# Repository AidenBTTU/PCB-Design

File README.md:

This repository holds the Custom PCB Design I have done during my degree so far. This includes a step counting device with I2C and USB communication, an external crystal oscillator, and a power system with battery charging capabilities aswell as a seperate PCB for driving motors.

# Step Count PCB V2

# Motor Driver PCB

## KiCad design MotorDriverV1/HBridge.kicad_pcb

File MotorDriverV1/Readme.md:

The motor driver pcb designed in this folder was designed to operate with 6V TT Motors from a Raspberry Pi Pico. A signal voltage taken off a shunt resistor is amplified on board to be sent to a seperate overcurrent detection board. The PCB is designed to be operated with 2-4 TT motors controlled in pairs. Connectors are designed with the Raspberry Pi Pico in mind. Current through motors is not designed to handle more than 2A collectively. LFWD & LREV, RFWD & RREV are exclusive pairs and should not be held high at the same time or else through-current is likely. Pull up resistors allow the board to be operated from a digital voltage supply, but signal pins have only been tested at 3.3V. Mosfets used are the readily available IRLZ44N and IRF4905. The resistor used should be 500mohm or greater if using long or thin cables, capable of handling at least 1W.

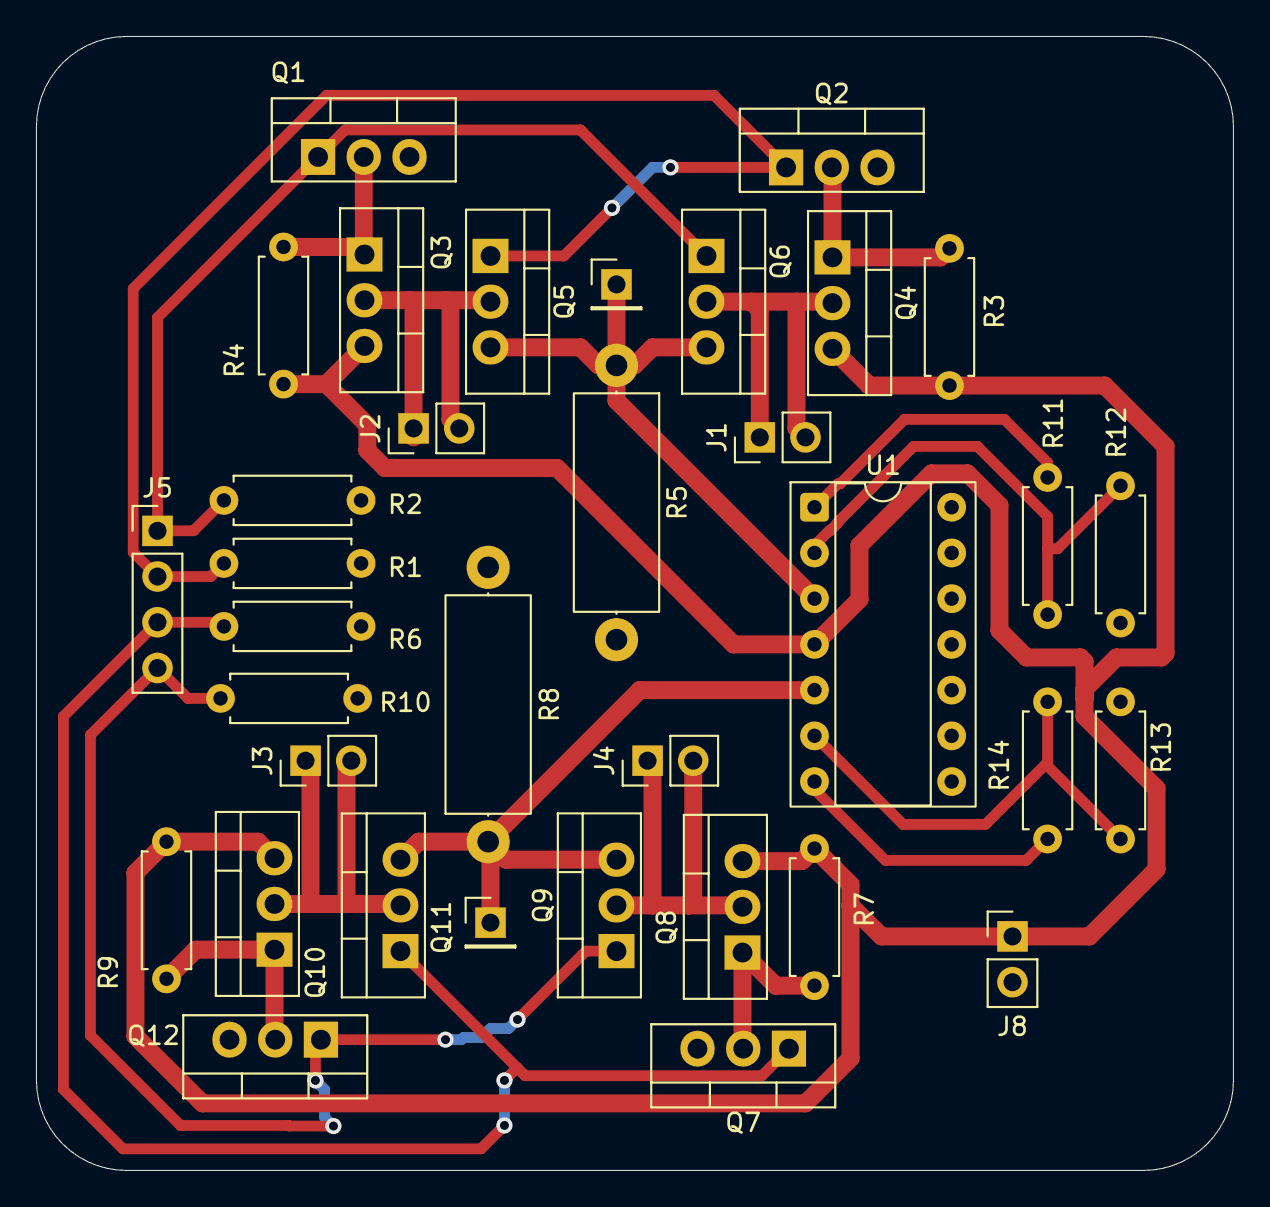
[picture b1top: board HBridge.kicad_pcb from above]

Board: 2 copper layers, 66.5 x 63.0 mm, 35 parts (0 on the bottom side), 20 nets.

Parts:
J1, J2, J3, J4, J8: Conn_01x02_Pin; PinHeader_1x02_P2.54mm_Vertical
J5: Conn_01x04_Pin; PinHeader_1x04_P2.54mm_Vertical
J6, J7: Conn_01x01_Pin; PinHeader_1x01_P2.54mm_Vertical
Q1, Q2, Q5, Q6, Q7, Q9, Q11, Q12: IRLZ44N; TO-220-3_Vertical
Q3, Q4, Q8, Q10: IRF4905; TO-220-3_Vertical
R1, R2, R3, R4, R6, R7, R9, R10: 100k; R_Axial_DIN0207_L6.3mm_D2.5mm_P7.62mm_Horizontal
R5, R8: 0.01; R_Axial_DIN0414_L11.9mm_D4.5mm_P15.24mm_Horizontal
R11, R12, R13, R14: R; R_Axial_DIN0207_L6.3mm_D2.5mm_P7.62mm_Horizontal
U1: LM324; DIP-14_W7.62mm_Socket

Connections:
+5V: J8.1, Q3.3 (S), Q4.3 (S), Q8.3 (S), Q10.3 (S), R3.2, R4.2, R7.2, R9.2, U1.4 (V+)
/LM1: J1.1, J1.2, Q4.2 (D), Q6.2 (D)
/LM2: J2.1, J2.2, Q3.2 (D), Q5.2 (D)
/Lin1: J5.2, Q2.1 (G), Q5.1 (G), R1.1
/Lin2: J5.1, Q1.1 (G), Q6.1 (G), R2.1
/Lout: R11.2, U1.1
/RM1: J3.1, J3.2, Q10.2 (D), Q11.2 (D)
/RM2: J4.1, J4.2, Q8.2 (D), Q9.2 (D)
/Rin1: J5.4, Q9.1 (G), Q12.1 (G), R10.1
/Rin2: J5.3, Q7.1 (G), Q11.1 (G), R6.1
/Rout: R14.2, U1.7
/VSL: J6.1, Q5.3 (S), Q6.3 (S), R5.1, U1.3 (+)
/VSR: J7.1, Q9.3 (S), Q11.3 (S), R8.1, U1.5 (+)
GND: J8.2, Q1.3 (S), Q2.3 (S), Q7.3 (S), Q12.3 (S), R1.2, R2.2, R5.2, R6.2, R8.2, R10.2, R12.1, R13.1, U1.11 (V-)
unnamed: Q1.2 (D), Q3.1 (G), R4.1
unnamed: Q2.2 (D), Q4.1 (G), R3.1
unnamed: Q7.2 (D), Q8.1 (G), R7.1
unnamed: Q10.1 (G), Q12.2 (D), R9.1
unnamed: R11.1, R12.2, U1.2 (-)
unnamed: R13.2, R14.1, U1.6 (-)

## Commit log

2026-04-25 Create Motor Driver
2026-04-25 Add image to Motor Driver documentation
2026-04-25 Revise README with project details and images
    Updated project description and added images for Step Count PCB V2 and Motor Driver PCB.
2026-04-25 Update README.md for clarity and corrections
    Revised the introduction for clarity and corrected spelling errors.
2026-04-25 Add README for MotorDriverV1 PCB details
2026-04-25 Update Readme with motor current and component info
    Added details about current handling and component specifications.
2026-04-25 PCB and schematic files
2026-04-25 Replace autosave PCB file with final version
2026-04-25 Update HBridge schematic file
2026-04-25 Revise resistor requirements in Readme.md
2026-04-25 LTSpice simulation files
